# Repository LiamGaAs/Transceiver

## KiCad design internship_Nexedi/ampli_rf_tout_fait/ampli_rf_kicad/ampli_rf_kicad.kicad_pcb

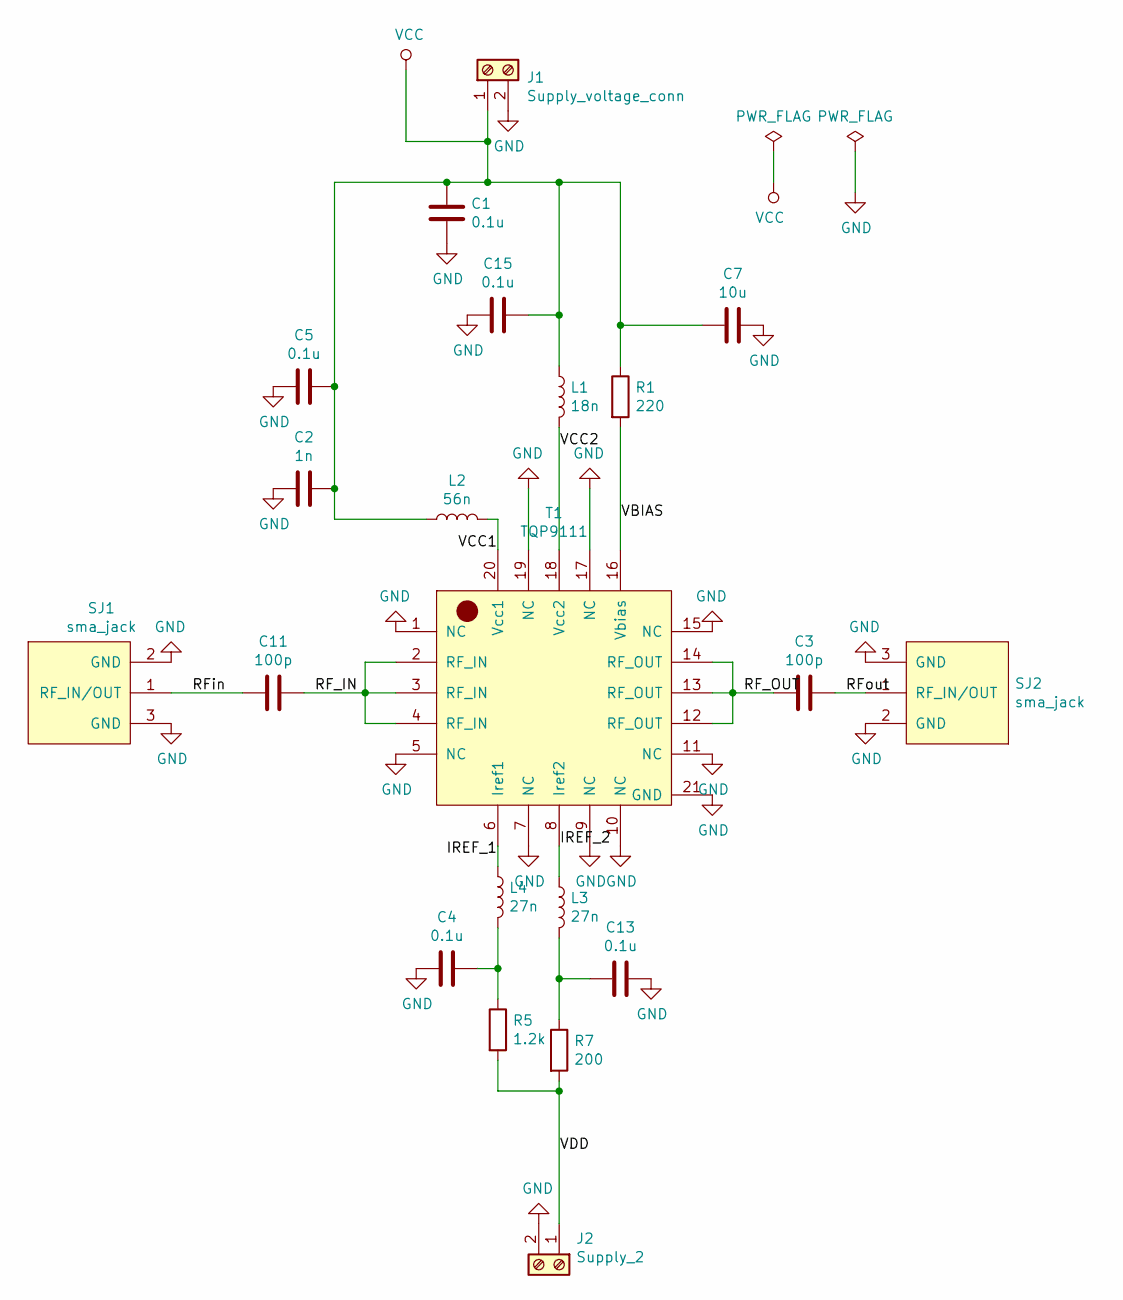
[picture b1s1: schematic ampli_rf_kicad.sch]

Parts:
C1, C4, C5, C13, C15: 0.1u; CP_EIA-3216-10_Kemet-I_Pad1.58x1.35mm_HandSolder
C2: 1n; CP_EIA-3216-10_Kemet-I_Pad1.58x1.35mm_HandSolder
C3, C11: 100p; CP_EIA-3216-10_Kemet-I_Pad1.58x1.35mm_HandSolder
C7: 10u; CP_EIA-3216-10_Kemet-I_Pad1.58x1.35mm_HandSolder
J1: Supply_voltage_conn; PRT-08084
J2: Supply_2; PRT-08084
L1: 18n; 18nH_1900MHz
L2: 56n; L_0603_1608Metric_Pad1.05x0.95mm_HandSolder
L3, L4: 27n; L_0603_1608Metric_Pad1.05x0.95mm_HandSolder
R1: 220; R_1206_3216Metric_Pad1.42x1.75mm_HandSolder
R5: 1.2k; R_1206_3216Metric_Pad1.42x1.75mm_HandSolder
R7: 200; R_1206_3216Metric_Pad1.42x1.75mm_HandSolder
SJ1, SJ2: sma_jack; CONSMA003.062-G
T1: TQP9111

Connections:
/IREF_1: L4.1, T1.6 (Iref1)
/IREF_2: L3.1, T1.8 (Iref2)
/RF_IN: C11.1, T1.2 (RF_IN), T1.3 (RF_IN), T1.4 (RF_IN)
/RF_OUT: C3.2, T1.12 (RF_OUT), T1.13 (RF_OUT), T1.14 (RF_OUT)
/RFin: C11.2, SJ1.1 (RF_IN/OUT)
/RFout: C3.1, SJ2.1 (RF_IN/OUT)
/VBIAS: R1.2, T1.16 (Vbias)
/VCC1: L2.2, T1.20 (Vcc1)
/VCC2: L1.2, T1.18 (Vcc2)
/VDD: J2.1, R5.2, R7.2
GND: C1.2, C2.2, C4.2, C5.2, C7.1, C13.1, C15.2, J1.2, J2.2, SJ1.2 (GND), SJ1.3 (GND), SJ2.2 (GND), SJ2.3 (GND), T1.1 (NC), T1.5 (NC), T1.7 (NC), T1.9 (NC), T1.10 (NC), T1.11 (NC), T1.15 (NC), T1.17 (NC), T1.19 (NC), T1.21 (GND)
unnamed: C4.1, L4.2, R5.1
unnamed: C13.2, L3.2, R7.1
VCC: C1.1, C2.1, C5.1, C7.2, C15.1, J1.1, L1.1, L2.1, R1.1

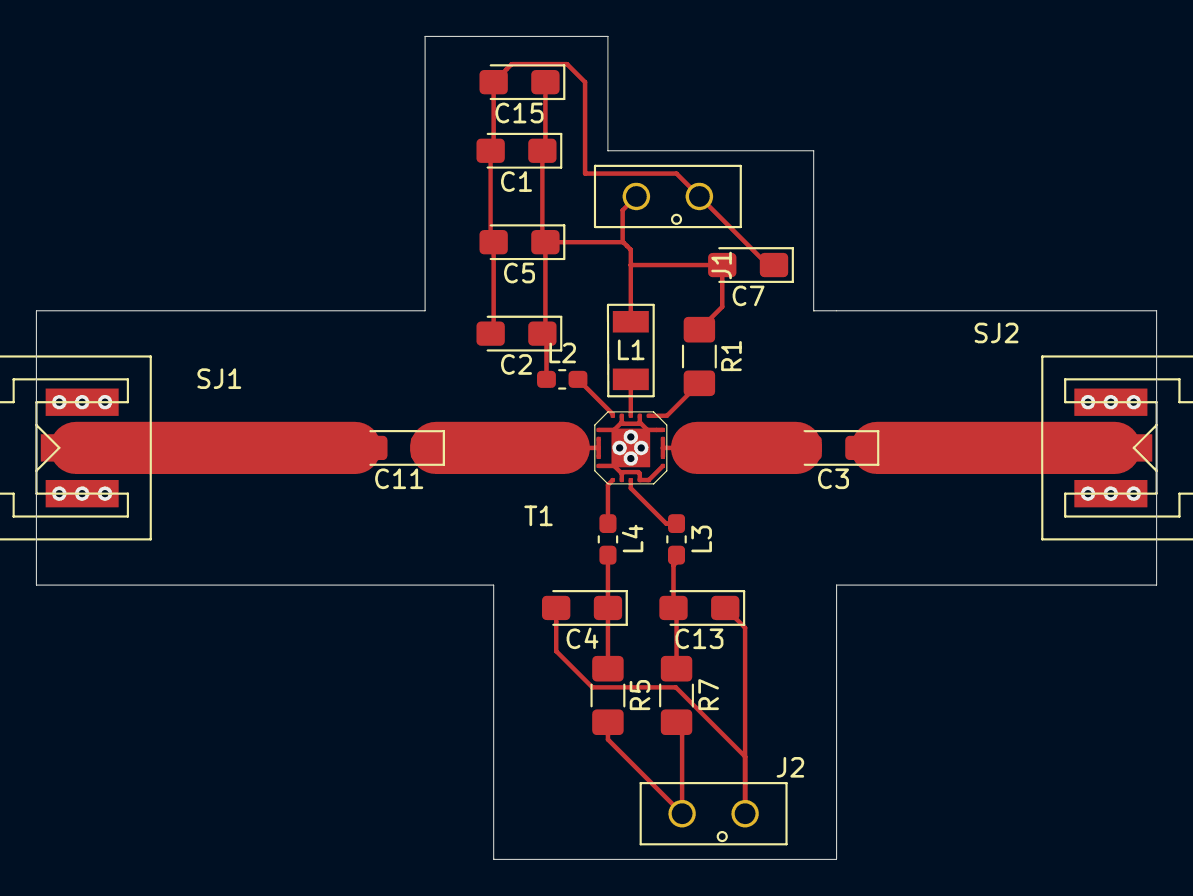
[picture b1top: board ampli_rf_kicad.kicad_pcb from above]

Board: 2 copper layers, 62.2 x 45.7 mm, 21 parts (0 on the bottom side), 14 nets.

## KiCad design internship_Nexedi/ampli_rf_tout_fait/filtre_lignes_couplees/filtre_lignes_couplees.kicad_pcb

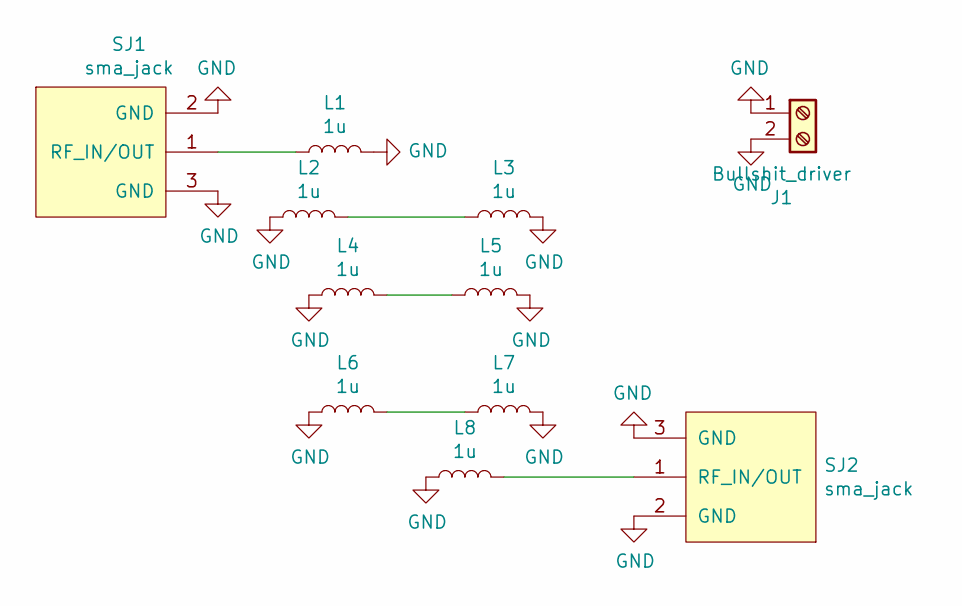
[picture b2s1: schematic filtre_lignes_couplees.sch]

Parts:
J1: Bullshit_driver; PRT-08084
L1, L2, L3, L4, L5, L6, L7, L8: 1u; L_0603_1608Metric_Pad1.05x0.95mm_HandSolder
SJ1, SJ2: sma_jack; CONSMA003.062-G

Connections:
GND: J1.1, J1.2, L1.2, L2.1, L3.2, L4.1, L5.2, L6.1, L7.2, L8.1, SJ1.2 (GND), SJ1.3 (GND), SJ2.2 (GND), SJ2.3 (GND)
unnamed: L1.1, SJ1.1 (RF_IN/OUT)
unnamed: L2.2, L3.1
unnamed: L4.2, L5.1
unnamed: L6.2, L7.1
unnamed: L8.2, SJ2.1 (RF_IN/OUT)

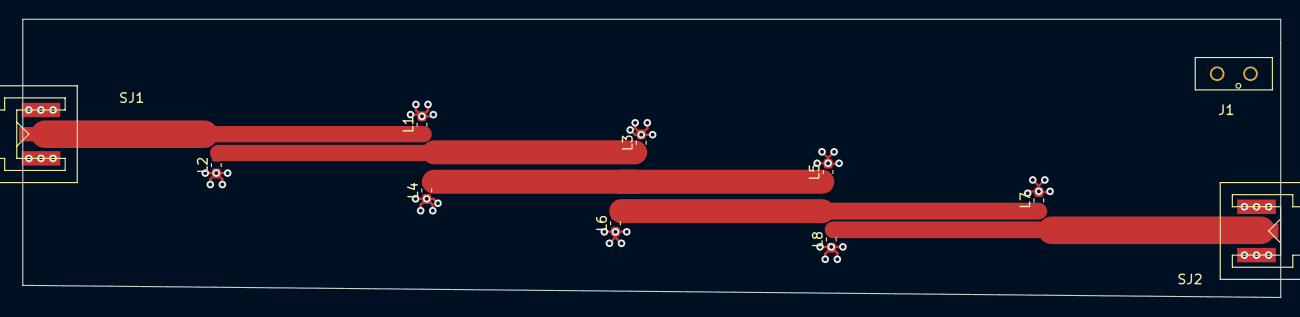
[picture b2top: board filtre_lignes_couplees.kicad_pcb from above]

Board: 2 copper layers, 132.1 x 29.2 mm, 11 parts (0 on the bottom side), 6 nets.

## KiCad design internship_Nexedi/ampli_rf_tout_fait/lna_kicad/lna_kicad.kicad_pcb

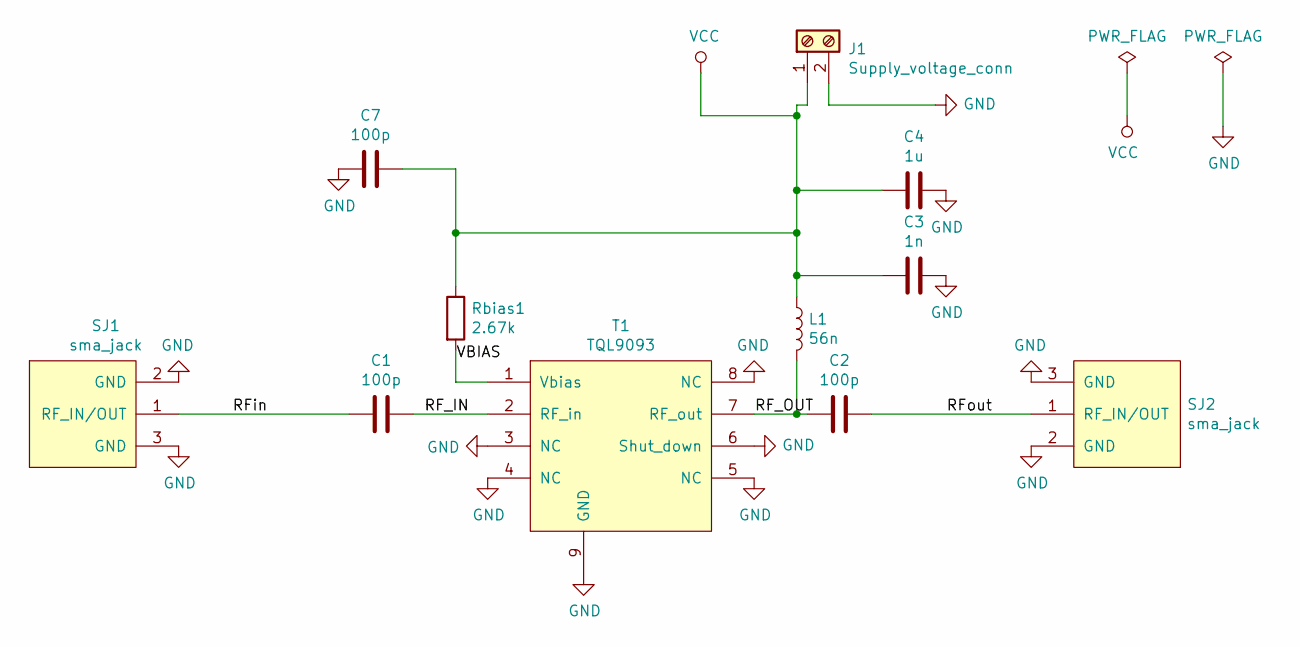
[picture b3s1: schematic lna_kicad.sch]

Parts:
C1, C2, C7: 100p; CP_EIA-3216-10_Kemet-I_Pad1.58x1.35mm_HandSolder
C3: 1n; CP_EIA-3216-10_Kemet-I_Pad1.58x1.35mm_HandSolder
C4: 1u; CP_EIA-3216-10_Kemet-I_Pad1.58x1.35mm_HandSolder
J1: Supply_voltage_conn; PRT-08084
L1: 56n; L_0603_1608Metric_Pad1.05x0.95mm_HandSolder
Rbias1: 2.67k; R_1206_3216Metric_Pad1.42x1.75mm_HandSolder
SJ1, SJ2: sma_jack; CONSMA003.062-G
T1: TQL9093

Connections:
/RF_IN: C1.1, T1.2 (RF_in)
/RF_OUT: C2.2, L1.2, T1.7 (RF_out)
/RFin: C1.2, SJ1.1 (RF_IN/OUT)
/RFout: C2.1, SJ2.1 (RF_IN/OUT)
/VBIAS: Rbias1.2, T1.1 (Vbias)
GND: C3.1, C4.1, C7.2, J1.2, SJ1.2 (GND), SJ1.3 (GND), SJ2.2 (GND), SJ2.3 (GND), T1.3 (NC), T1.4 (NC), T1.5 (NC), T1.6 (Shut_down), T1.8 (NC), T1.9 (GND)
VCC: C3.2, C4.2, C7.1, J1.1, L1.1, Rbias1.1

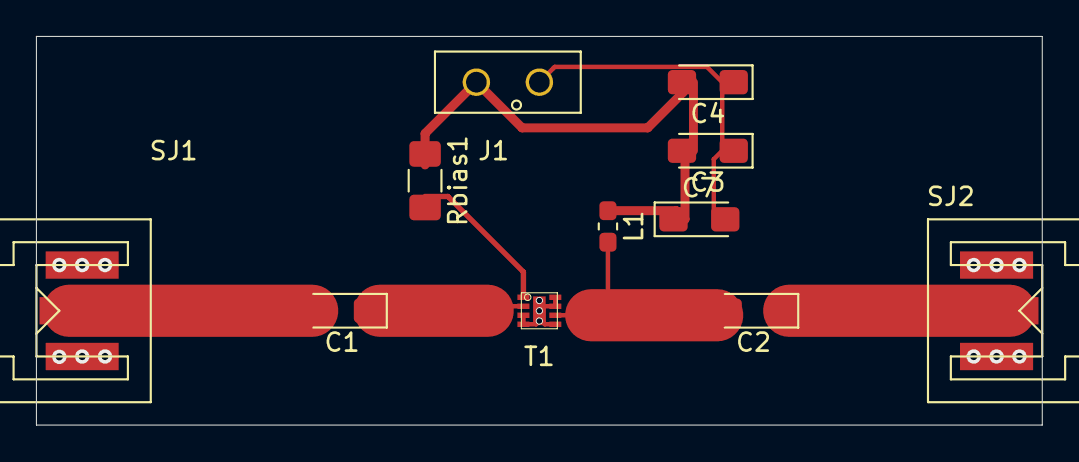
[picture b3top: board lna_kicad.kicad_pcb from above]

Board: 2 copper layers, 55.9 x 21.6 mm, 11 parts (0 on the bottom side), 7 nets.

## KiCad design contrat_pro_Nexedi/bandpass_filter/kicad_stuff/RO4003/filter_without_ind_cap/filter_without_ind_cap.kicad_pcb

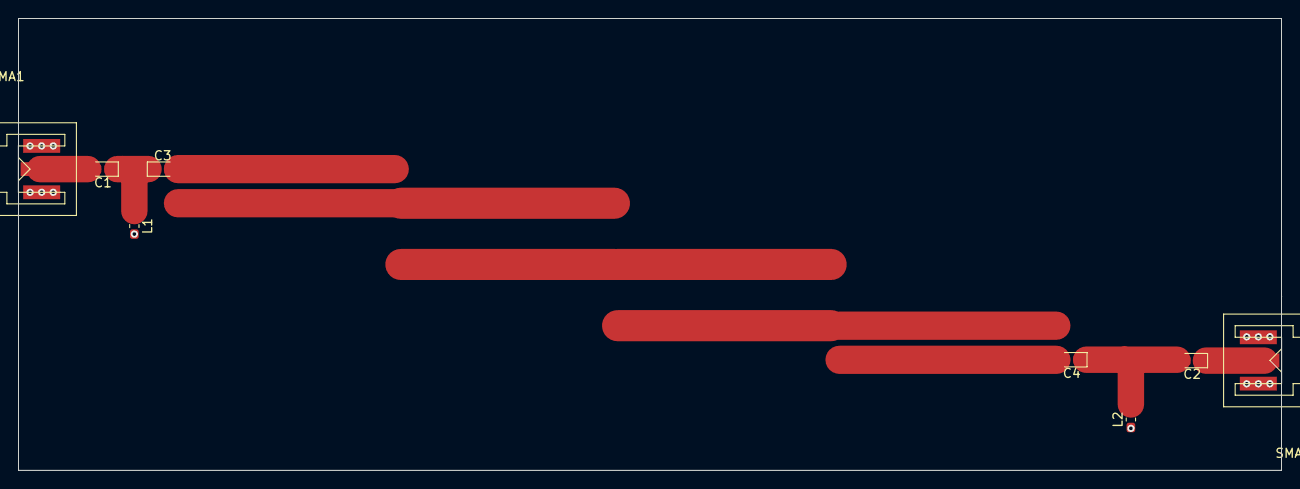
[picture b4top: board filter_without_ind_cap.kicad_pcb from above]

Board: 2 copper layers, 138.4 x 49.5 mm, 8 parts (0 on the bottom side), 5 nets.

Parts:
C1, C2: 10n; CP_EIA-1608-08_AVX-J_Pad1.25x1.05mm_HandSolder
C3, C4: 3.9p; CP_EIA-1608-08_AVX-J_Pad1.25x1.05mm_HandSolder
L1, L2: 5.1n; L_0603_1608Metric_Pad1.05x0.95mm_HandSolder
SMA1, SMA2: sma_connector; CONSMA003.062-G

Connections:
GND: L1.2, L2.1, SMA1.2, SMA1.3, SMA2.2, SMA2.3
unnamed: C1.1, C3.1, L1.1
unnamed: C1.2, SMA1.1
unnamed: C2.1, SMA2.1
unnamed: C2.2, C4.1, L2.2

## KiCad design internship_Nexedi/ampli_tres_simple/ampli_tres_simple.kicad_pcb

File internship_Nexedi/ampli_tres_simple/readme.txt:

In order to achieve the DC analysis of the circuit.

Once you have finished to draw your schematic : 

1 : Goto "Generate netlist file"

2 : Go in "Spice" tab.

3 : Check "defaut format" option.

4 : save the generated file (a .cir file) to the wanted location

5 : open this file with a text editor and add .OP at the just before the .end line
Thanks to this, you will be able to achieve a dc analysis of your circuit

5 : Once saved,open a terminal and go to the repository where your .cir file has been saved

6 : Type "ngspice nameofyourfile.cir" . Then type "run".
Normally, a line named "No. of Data Rows : 1 " shoud appear. If yes, it means the dc analysis has been taken into account.

7 : Then, to print a voltage , type "print v(nameofthepad)" in order to see the voltage of a given pad. A pad (or label) name could be "Vc" for the collector voltage, for example.
print v(Vc) woud print the collector's voltage.

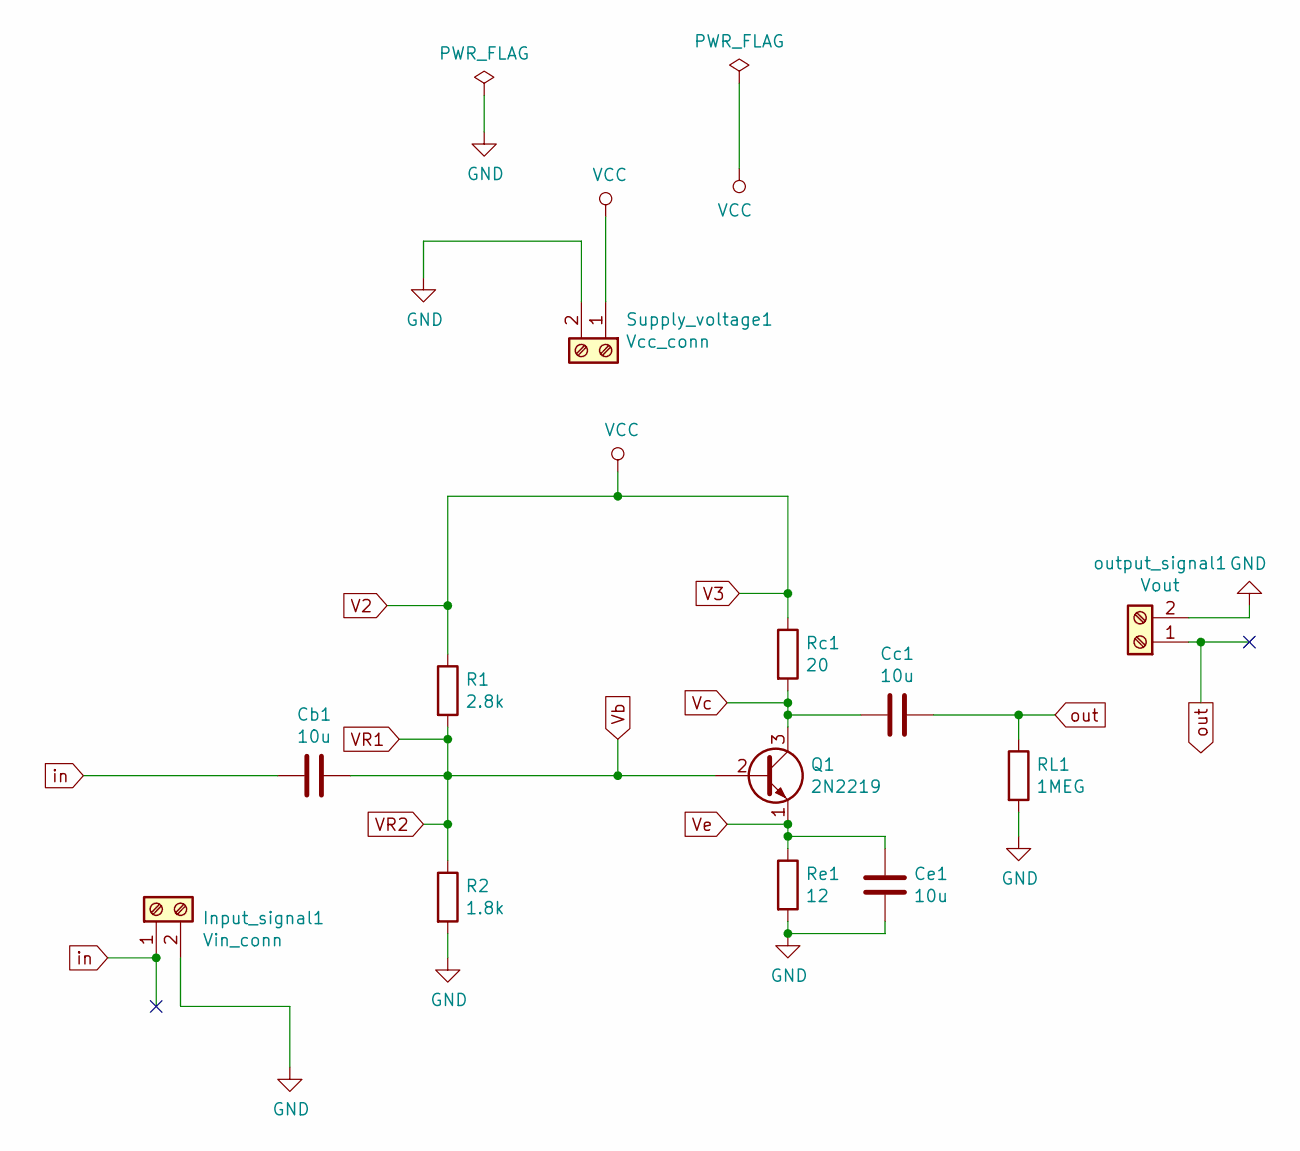
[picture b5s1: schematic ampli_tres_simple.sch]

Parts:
Cb1: 10u; CP_EIA-3216-10_Kemet-I_Pad1.58x1.35mm_HandSolder
Cc1: 10u; CP_EIA-3216-10_Kemet-I_Pad1.58x1.35mm_HandSolder
Ce1: 10u; CP_EIA-3216-10_Kemet-I_Pad1.58x1.35mm_HandSolder
Input_signal1: Vin_conn; PRT-08084
Q1: 2N2219
R1: 2.8k; R_0603_1608Metric_Pad1.05x0.95mm_HandSolder
R2: 1.8k; R_0402_1005Metric
RL1: 1MEG; R_1206_3216Metric_Pad1.42x1.75mm_HandSolder
Rc1: 20; R_1020_2550Metric_Pad1.33x5.20mm_HandSolder
Re1: 12; R_1206_3216Metric_Pad1.42x1.75mm_HandSolder
Supply_voltage1: Vcc_conn; PRT-08084
output_signal1: Vout; PRT-08084

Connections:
GND: Ce1.2, Input_signal1.2, R2.2, RL1.2, Re1.2, Supply_voltage1.2, output_signal1.2
V2: R1.1, Rc1.1, Supply_voltage1.1
VR1: Cb1.1, Q1.2 (B), R1.2, R2.1
Vc: Cc1.2, Q1.3 (C), Rc1.2
Ve: Ce1.1, Q1.1 (E), Re1.1
in: Cb1.2, Input_signal1.1
out: Cc1.1, RL1.1, output_signal1.1

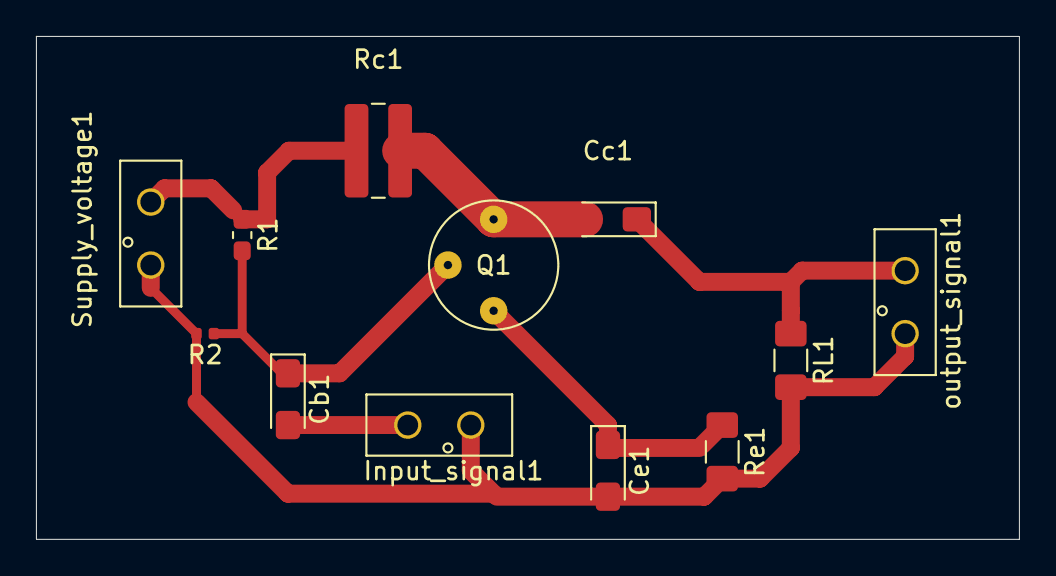
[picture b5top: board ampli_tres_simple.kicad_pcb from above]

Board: 2 copper layers, 54.6 x 27.9 mm, 12 parts (0 on the bottom side), 7 nets.

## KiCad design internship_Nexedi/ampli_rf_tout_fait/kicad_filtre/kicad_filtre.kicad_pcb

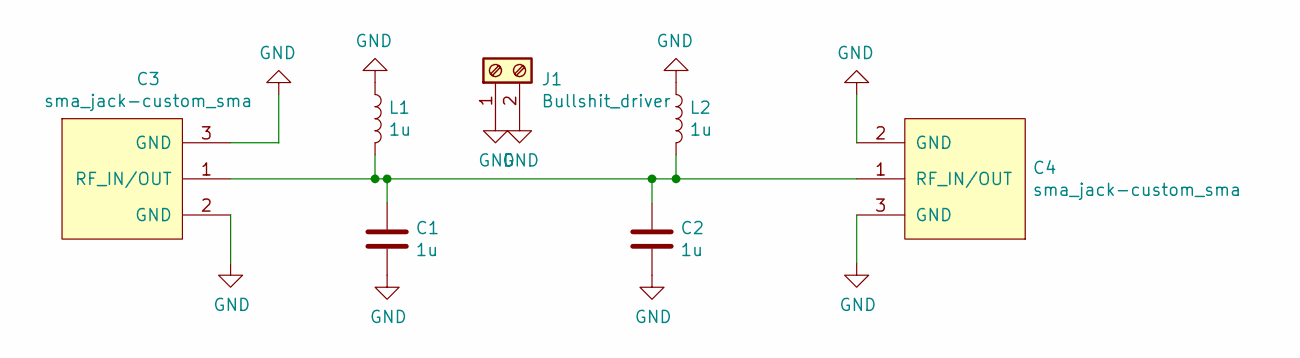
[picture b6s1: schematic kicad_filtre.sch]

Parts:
C1, C2: 1u; CP_EIA-1608-08_AVX-J_Pad1.25x1.05mm_HandSolder
C3, C4: sma_jack-custom_sma; CONSMA003.062-G
J1: Bullshit_driver; PRT-08084
L1, L2: 1u; L_0603_1608Metric_Pad1.05x0.95mm_HandSolder

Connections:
GND: C1.2, C2.2, C3.2 (GND), C3.3 (GND), C4.2 (GND), C4.3 (GND), J1.1, J1.2, L1.1, L2.1
unnamed: C1.1, C2.1, C3.1 (RF_IN/OUT), C4.1 (RF_IN/OUT), L1.2, L2.2

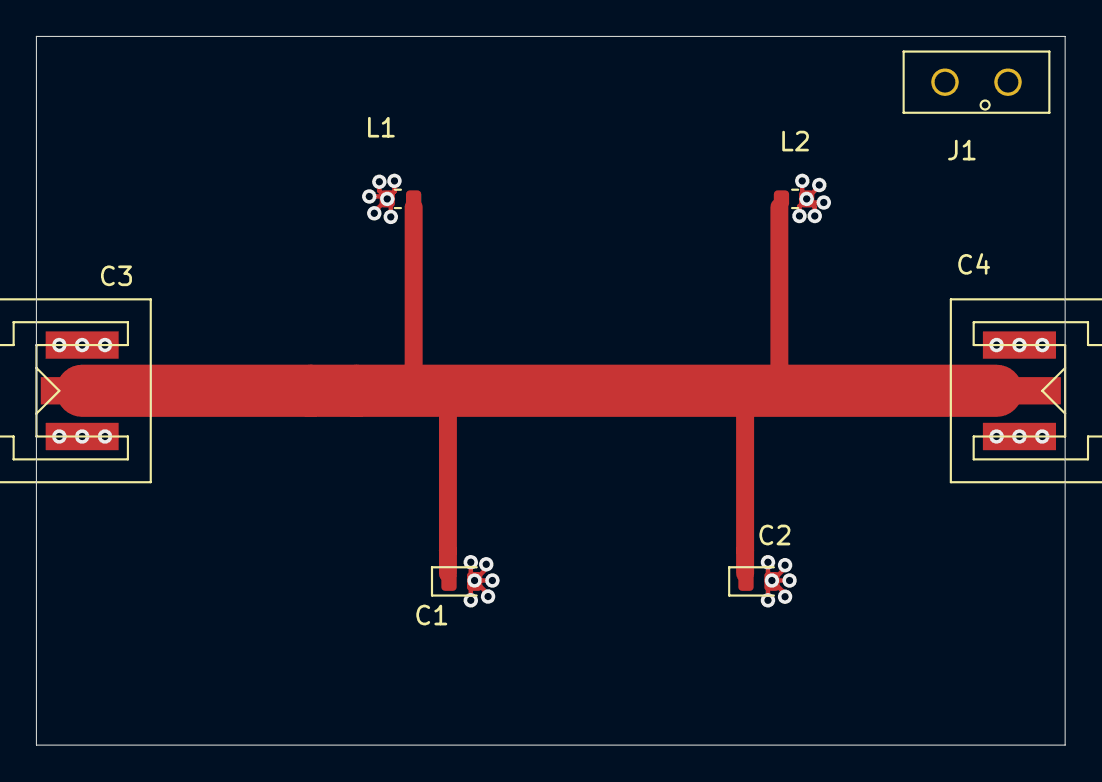
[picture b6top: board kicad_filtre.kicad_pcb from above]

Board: 2 copper layers, 57.2 x 39.4 mm, 7 parts (0 on the bottom side), 2 nets.

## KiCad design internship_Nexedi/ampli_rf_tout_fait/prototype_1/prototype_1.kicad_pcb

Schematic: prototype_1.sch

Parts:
C1, C2: 2p; CP_EIA-3216-10_Kemet-I_Pad1.58x1.35mm_HandSolder
C3: 0.1u; CP_EIA-3216-10_Kemet-I_Pad1.58x1.35mm_HandSolder
C4, C5: 100p; CP_EIA-3216-10_Kemet-I_Pad1.58x1.35mm_HandSolder
F1: F1958
J1: Supply; PRT-08084
R1, R2: 5k; R_1206_3216Metric_Pad1.42x1.75mm_HandSolder
SJ1, SJ2: sma_jack; CONSMA003.062-G

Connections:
/D2_in: C1.1, F1.23, R1.2
/D5_in: C2.2, F1.20, R2.2
/RF_OUT: C4.1, SJ2.1 (RF_IN/OUT)
/RF_in: C5.1, F1.5
/RF_out: C4.2, F1.14
/RFin: C5.2, SJ1.1 (RF_IN/OUT)
GND: C1.2, C2.1, C3.1, F1.1, F1.3, F1.4, F1.6, F1.7, F1.8, F1.9, F1.10, F1.11, F1.12, F1.13, F1.15, F1.17, F1.18, F1.19, F1.21, F1.22, F1.24, F1.25, J1.2, SJ1.2 (GND), SJ1.3 (GND), SJ2.2 (GND), SJ2.3 (GND)
VCC: C3.2, F1.2, F1.16, J1.1, R1.1, R2.1

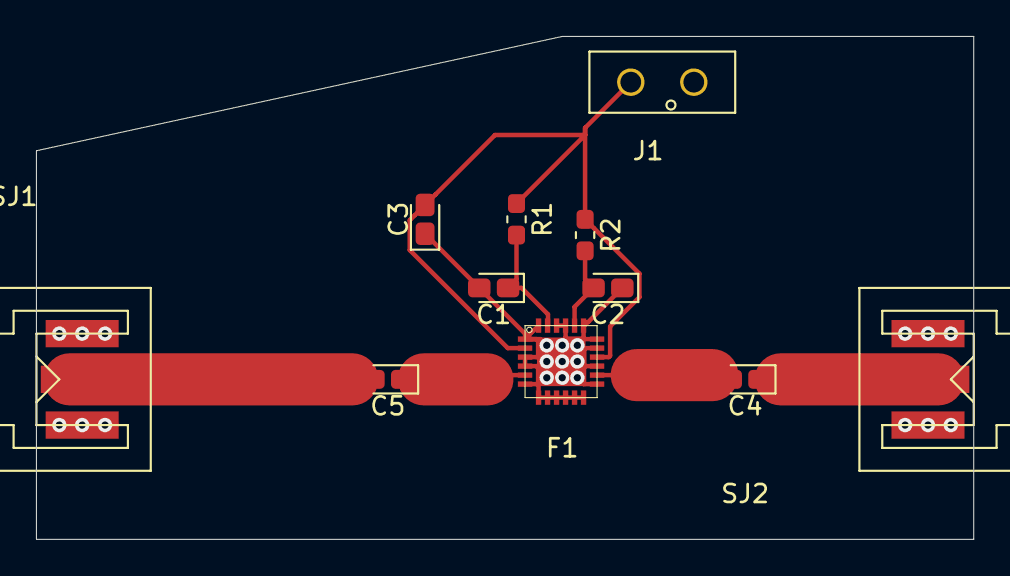
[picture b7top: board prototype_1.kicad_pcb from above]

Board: 2 copper layers, 52.1 x 27.9 mm, 11 parts (0 on the bottom side), 8 nets.

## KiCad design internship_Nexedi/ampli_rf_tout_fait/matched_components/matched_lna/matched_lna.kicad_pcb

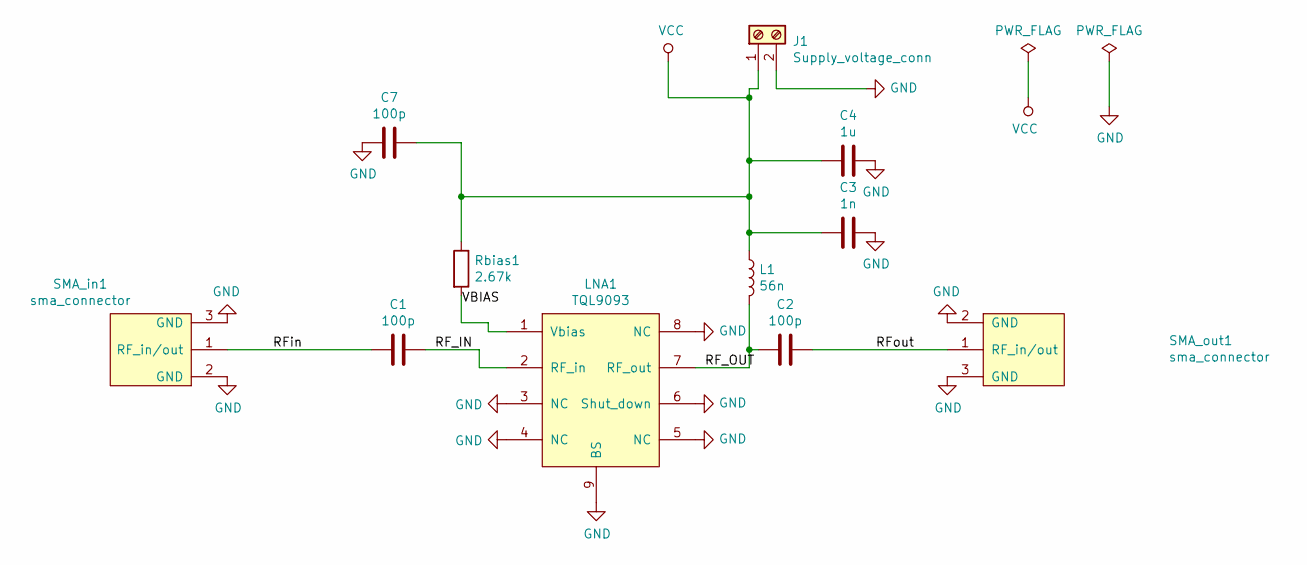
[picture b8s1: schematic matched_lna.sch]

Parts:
C1, C2, C7: 100p; CP_EIA-3216-10_Kemet-I_Pad1.58x1.35mm_HandSolder
C3: 1n; CP_EIA-3216-10_Kemet-I_Pad1.58x1.35mm_HandSolder
C4: 1u; CP_EIA-3216-10_Kemet-I_Pad1.58x1.35mm_HandSolder
J1: Supply_voltage_conn; PRT-08084
L1: 56n; L_0603_1608Metric_Pad1.05x0.95mm_HandSolder
LNA1: TQL9093
Rbias1: 2.67k; R_1206_3216Metric_Pad1.42x1.75mm_HandSolder
SMA_in1: sma_connector; CONSMA003.062-G
SMA_out1: sma_connector; CONSMA003.062-G

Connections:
/RF_IN: C1.1, LNA1.2 (RF_in)
/RF_OUT: C2.2, L1.2, LNA1.7 (RF_out)
/RFin: C1.2, SMA_in1.1 (RF_in/out)
/RFout: C2.1, SMA_out1.1 (RF_in/out)
/VBIAS: LNA1.1 (Vbias), Rbias1.2
GND: C3.1, C4.1, C7.2, J1.2, LNA1.3 (NC), LNA1.4 (NC), LNA1.5 (NC), LNA1.6 (Shut_down), LNA1.8 (NC), LNA1.9 (BS), SMA_in1.2 (GND), SMA_in1.3 (GND), SMA_out1.2 (GND), SMA_out1.3 (GND)
VCC: C3.2, C4.2, C7.1, J1.1, L1.1, Rbias1.1

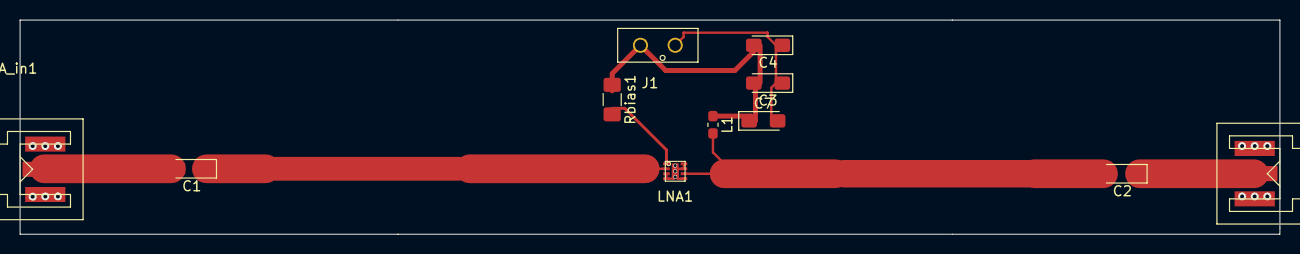
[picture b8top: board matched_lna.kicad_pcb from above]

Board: 2 copper layers, 127.0 x 21.6 mm, 11 parts (0 on the bottom side), 7 nets.

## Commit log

2019-11-14 nouveau fichier : contrat_pro_Nexedi/ampli_transistor/fet_transistor/GF2965-SM-1504678.pdf nouveau fichier : contrat_pro_Nexedi/ampli_transistor/fet_transistor/GF2978-SM-1506841.pdf nouveau fichier :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
